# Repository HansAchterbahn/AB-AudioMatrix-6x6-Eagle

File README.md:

# AB AudioMatrix 6x6

Active audio matrix (6x6), which can map 6 input channels to 6 output channels. Connection via 3.5 jack cable. Compatible with line signals (aux, headphones, active speakers, ...).

*Fork me and have fun!*

## Pictures

## Schematic

## Board

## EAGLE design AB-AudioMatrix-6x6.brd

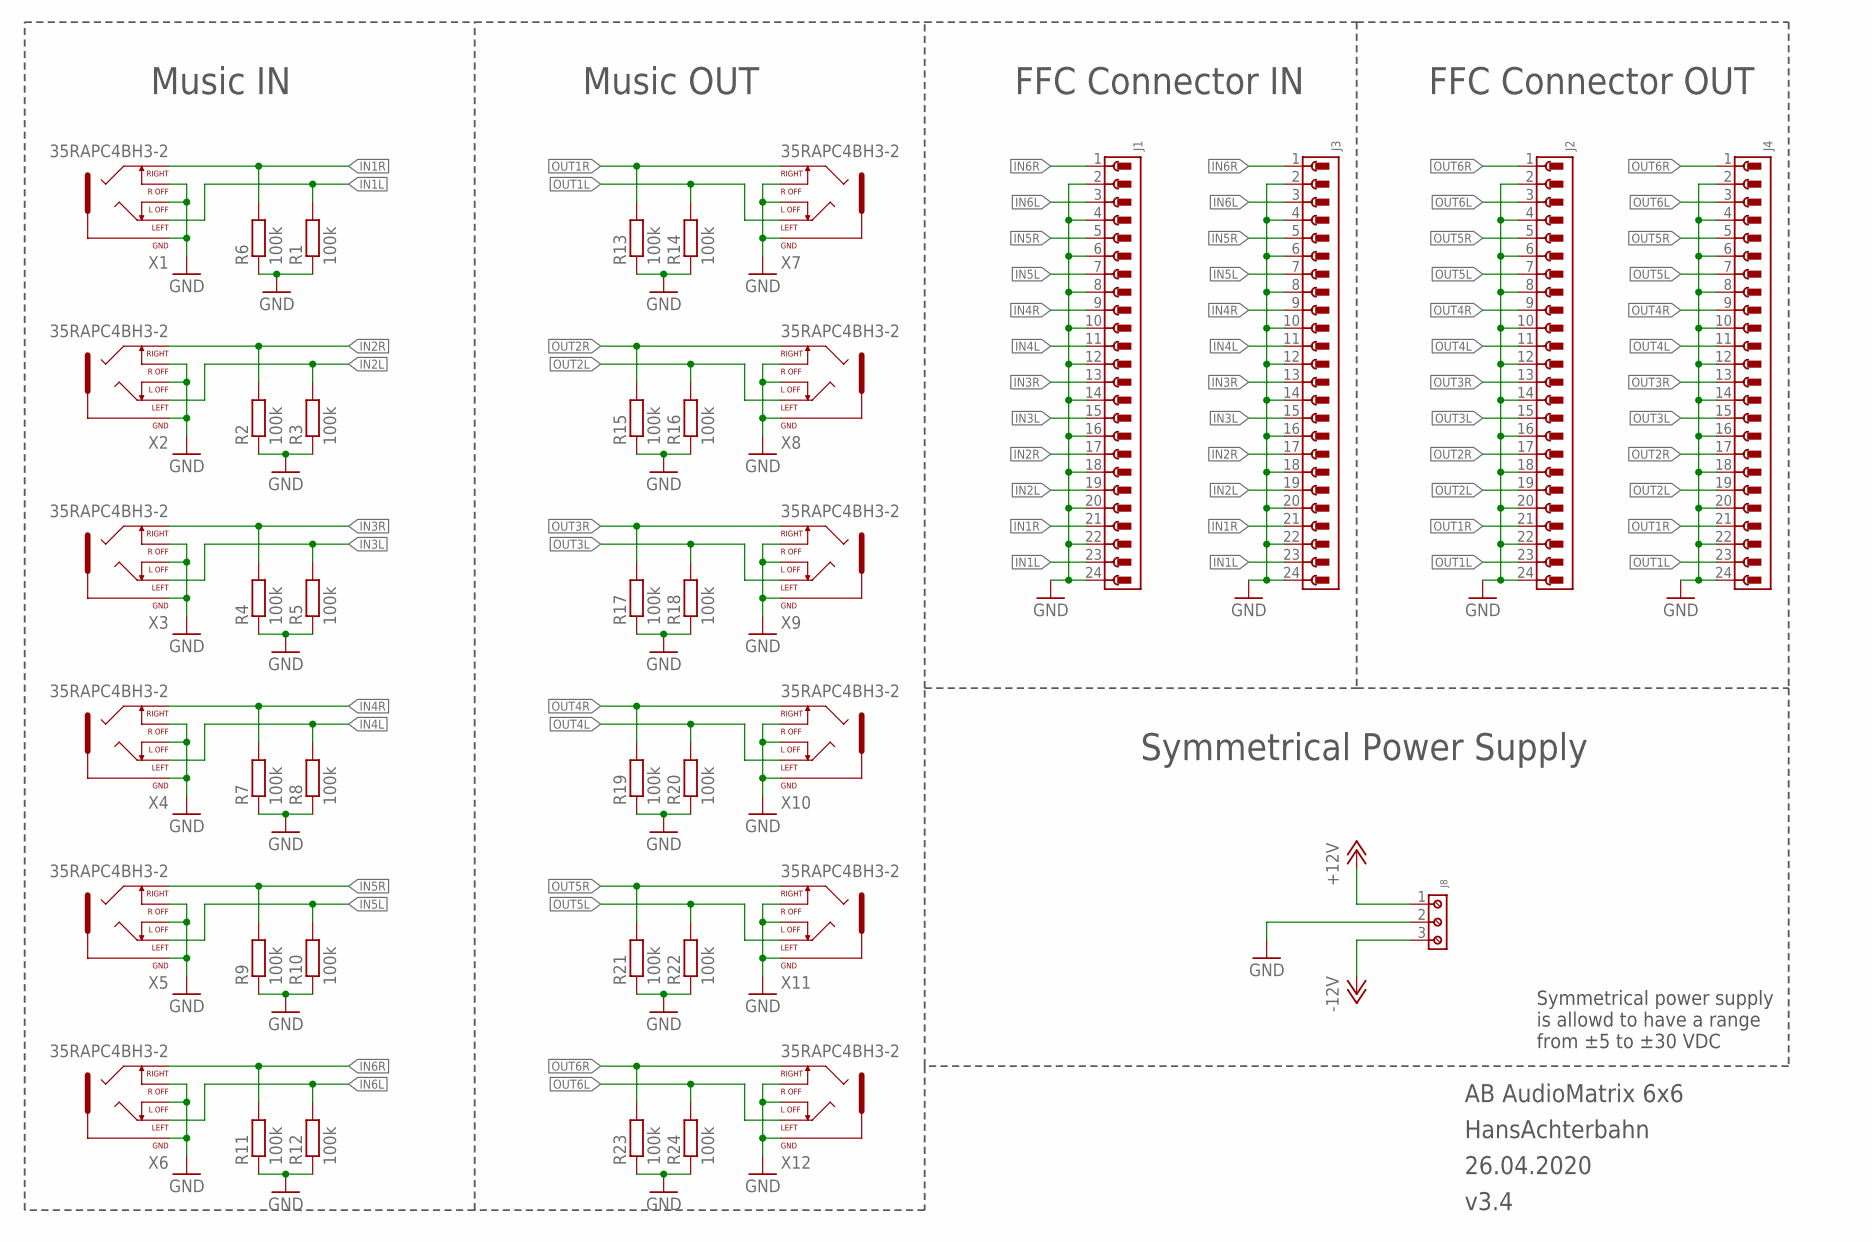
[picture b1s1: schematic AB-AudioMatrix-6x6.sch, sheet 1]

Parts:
J1, J2, J3, J4: 6861XX188622_686124188622; 686124188622
J8: 691102710003
R1, R2, R3, R4, R5, R6, R7, R8, R9, R10, R11, R12, R13, R14, R15, R16, R17, R18, R19, R20, R21, R22, R23, R24: 100k; R0603; MOUSER 71-CRCW0603-100K-E3
X1: 35RAPC4BH3-2; SWITCHCRAFT_35RAPC4BH3; MOUSER 502-35RAPC4BH3
X2, X3, X4, X5, X6, X7, X8, X9, X10, X11, X12: 35RAPC4BH3-2; SWITCHCRAFT_35RAPC4BH3

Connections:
+12V: J8.1; also elsewhere on the board
-12V: J8.3; also elsewhere on the board
GND: J1.2, J1.4, J1.6, J1.8, J1.10, J1.12, J1.14, J1.16, J1.18, J1.20, J1.22, J1.24, J2.2, J2.4, J2.6, J2.8, J2.10, J2.12, J2.14, J2.16, J2.18, J2.20, J2.22, J2.24, J3.2, J3.4, J3.6, J3.8, J3.10, J3.12, J3.14, J3.16, J3.18, J3.20, J3.22, J3.24, J4.2, J4.4, J4.6, J4.8, J4.10, J4.12, J4.14, J4.16, J4.18, J4.20, J4.22, J4.24, J8.2, R1.1, R2.1, R3.1, R4.1, R5.1, R6.1, R7.1, R8.1, R9.1, R10.1, R11.1, R12.1, R13.1, R14.1, R15.1, R16.1, R17.1, R18.1, R19.1, R20.1, R21.1, R22.1, R23.1, R24.1, X1.1 (GND), X1.3 (RIGHT_OFF), X1.4 (LEFT_OFF), X2.1 (GND), X2.3 (RIGHT_OFF), X2.4 (LEFT_OFF), X3.1 (GND), X3.3 (RIGHT_OFF), X3.4 (LEFT_OFF), X4.1 (GND), X4.3 (RIGHT_OFF), X4.4 (LEFT_OFF), X5.1 (GND), X5.3 (RIGHT_OFF), X5.4 (LEFT_OFF), X6.1 (GND), X6.3 (RIGHT_OFF), X6.4 (LEFT_OFF), X7.1 (GND), X7.3 (RIGHT_OFF), X7.4 (LEFT_OFF), X8.1 (GND), X8.3 (RIGHT_OFF), X8.4 (LEFT_OFF), X9.1 (GND), X9.3 (RIGHT_OFF), X9.4 (LEFT_OFF), X10.1 (GND), X10.3 (RIGHT_OFF), X10.4 (LEFT_OFF), X11.1 (GND), X11.3 (RIGHT_OFF), X11.4 (LEFT_OFF), X12.1 (GND), X12.3 (RIGHT_OFF), X12.4 (LEFT_OFF)
IN1L: J1.23, J3.23, R1.2, X1.5 (LEFT); also elsewhere on the board
IN1R: J1.21, J3.21, R6.2, X1.2 (RIGHT); also elsewhere on the board
IN2L: J1.19, J3.19, R3.2, X2.5 (LEFT); also elsewhere on the board
IN2R: J1.17, J3.17, R2.2, X2.2 (RIGHT); also elsewhere on the board
IN3L: J1.15, J3.15, R5.2, X3.5 (LEFT); also elsewhere on the board
IN3R: J1.13, J3.13, R4.2, X3.2 (RIGHT); also elsewhere on the board
IN4L: J1.11, J3.11, R8.2, X4.5 (LEFT); also elsewhere on the board
IN4R: J1.9, J3.9, R7.2, X4.2 (RIGHT); also elsewhere on the board
IN5L: J1.7, J3.7, R10.2, X5.5 (LEFT); also elsewhere on the board
IN5R: J1.5, J3.5, R9.2, X5.2 (RIGHT); also elsewhere on the board
IN6L: J1.3, J3.3, R12.2, X6.5 (LEFT); also elsewhere on the board
IN6R: J1.1, J3.1, R11.2, X6.2 (RIGHT); also elsewhere on the board
OUT1L: J2.23, J4.23, R14.2, X7.5 (LEFT); also elsewhere on the board
OUT1R: J2.21, J4.21, R13.2, X7.2 (RIGHT); also elsewhere on the board
OUT2L: J2.19, J4.19, R16.2, X8.5 (LEFT); also elsewhere on the board
OUT2R: J2.17, J4.17, R15.2, X8.2 (RIGHT); also elsewhere on the board
OUT3L: J2.15, J4.15, R18.2, X9.5 (LEFT); also elsewhere on the board
OUT3R: J2.13, J4.13, R17.2, X9.2 (RIGHT); also elsewhere on the board
OUT4L: J2.11, J4.11, R20.2, X10.5 (LEFT); also elsewhere on the board
OUT4R: J2.9, J4.9, R19.2, X10.2 (RIGHT); also elsewhere on the board
OUT5L: J2.7, J4.7, R22.2, X11.5 (LEFT); also elsewhere on the board
OUT5R: J2.5, J4.5, R21.2, X11.2 (RIGHT); also elsewhere on the board
OUT6L: J2.3, J4.3, R24.2, X12.5 (LEFT); also elsewhere on the board
OUT6R: J2.1, J4.1, R23.2, X12.2 (RIGHT); also elsewhere on the board

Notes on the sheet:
Music OUT
Music IN
FFC Connector IN
FFC Connector OUT
Symmetrical Power Supply
Symmetrical power supply is allowd to have a range from ±5 to ±30 VDC

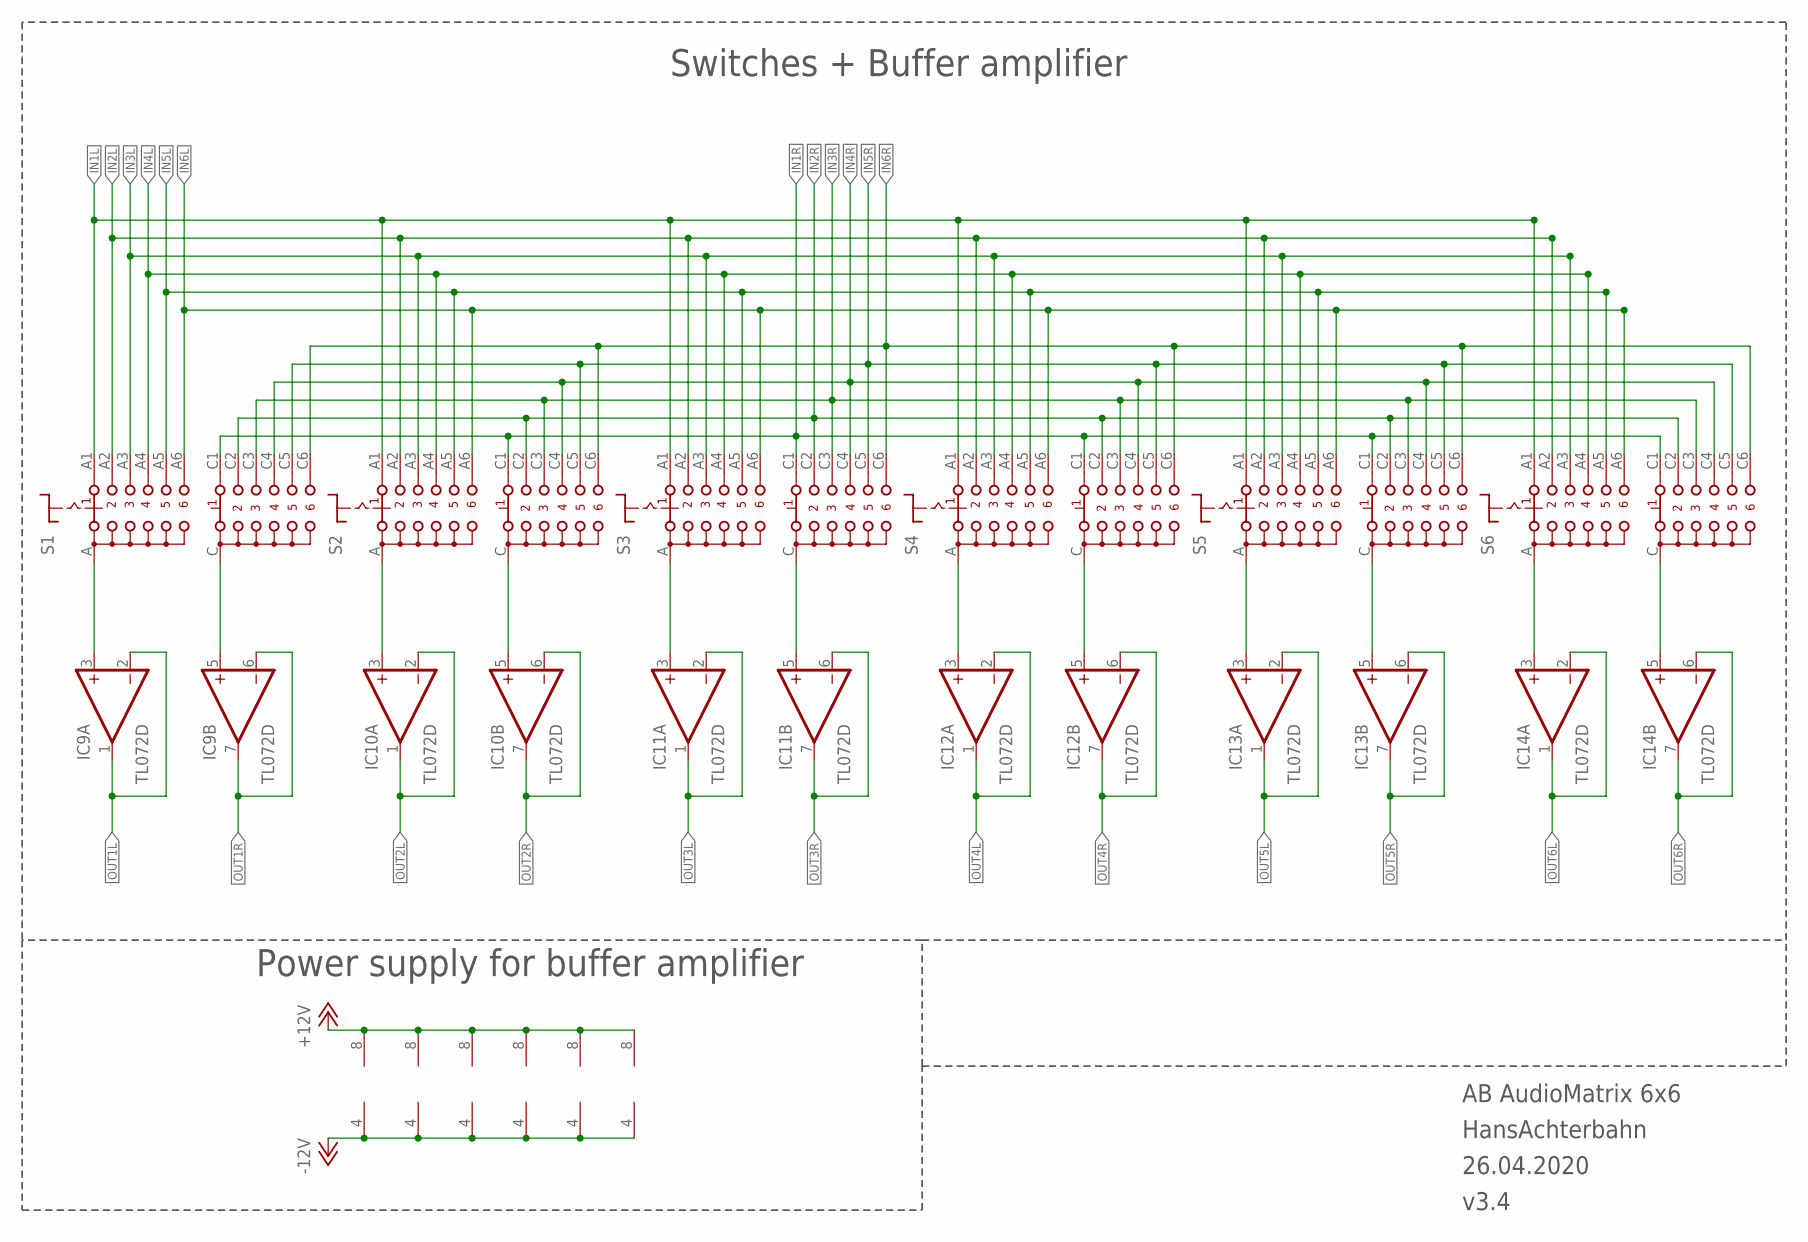
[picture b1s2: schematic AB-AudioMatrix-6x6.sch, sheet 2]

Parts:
IC9, IC10, IC11, IC12, IC13, IC14: TL072D; SO08
S1, S2, S3, S4, S5, S6: CK102X06

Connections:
+12V: IC9.8 (V+), IC10.8 (V+), IC11.8 (V+), IC12.8 (V+), IC13.8 (V+), IC14.8 (V+); also elsewhere on the board
-12V: IC9.4 (V-), IC10.4 (V-), IC11.4 (V-), IC12.4 (V-), IC13.4 (V-), IC14.4 (V-); also elsewhere on the board
IN1L: S1.A1, S2.A1, S3.A1, S4.A1, S5.A1, S6.A1; also elsewhere on the board
IN1R: S1.C1, S2.C1, S3.C1, S4.C1, S5.C1, S6.C1; also elsewhere on the board
IN2L: S1.A2, S2.A2, S3.A2, S4.A2, S5.A2, S6.A2; also elsewhere on the board
IN2R: S1.C2, S2.C2, S3.C2, S4.C2, S5.C2, S6.C2; also elsewhere on the board
IN3L: S1.A3, S2.A3, S3.A3, S4.A3, S5.A3, S6.A3; also elsewhere on the board
IN3R: S1.C3, S2.C3, S3.C3, S4.C3, S5.C3, S6.C3; also elsewhere on the board
IN4L: S1.A4, S2.A4, S3.A4, S4.A4, S5.A4, S6.A4; also elsewhere on the board
IN4R: S1.C4, S2.C4, S3.C4, S4.C4, S5.C4, S6.C4; also elsewhere on the board
IN5L: S1.A5, S2.A5, S3.A5, S4.A5, S5.A5, S6.A5; also elsewhere on the board
IN5R: S1.C5, S2.C5, S3.C5, S4.C5, S5.C5, S6.C5; also elsewhere on the board
IN6L: S1.A6, S2.A6, S3.A6, S4.A6, S5.A6, S6.A6; also elsewhere on the board
IN6R: S1.C6, S2.C6, S3.C6, S4.C6, S5.C6, S6.C6; also elsewhere on the board
unnamed: IC14.5 (+IN), S6.C
unnamed: IC14.3 (+IN), S6.A
unnamed: IC13.3 (+IN), S5.A
unnamed: IC12.3 (+IN), S4.A
unnamed: IC9.3 (+IN), S1.A
unnamed: IC12.5 (+IN), S4.C
unnamed: IC10.3 (+IN), S2.A
unnamed: IC13.5 (+IN), S5.C
unnamed: IC11.5 (+IN), S3.C
unnamed: IC11.3 (+IN), S3.A
unnamed: IC10.5 (+IN), S2.C
unnamed: IC9.5 (+IN), S1.C
OUT1L: IC9.1 (OUT), IC9.2 (-IN); also elsewhere on the board
OUT1R: IC9.6 (-IN), IC9.7 (OUT); also elsewhere on the board
OUT2L: IC10.1 (OUT), IC10.2 (-IN); also elsewhere on the board
OUT2R: IC10.6 (-IN), IC10.7 (OUT); also elsewhere on the board
OUT3L: IC11.1 (OUT), IC11.2 (-IN); also elsewhere on the board
OUT3R: IC11.6 (-IN), IC11.7 (OUT); also elsewhere on the board
OUT4L: IC12.1 (OUT), IC12.2 (-IN); also elsewhere on the board
OUT4R: IC12.6 (-IN), IC12.7 (OUT); also elsewhere on the board
OUT5L: IC13.1 (OUT), IC13.2 (-IN); also elsewhere on the board
OUT5R: IC13.6 (-IN), IC13.7 (OUT); also elsewhere on the board
OUT6L: IC14.1 (OUT), IC14.2 (-IN); also elsewhere on the board
OUT6R: IC14.6 (-IN), IC14.7 (OUT); also elsewhere on the board

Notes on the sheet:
Switches + Buffer amplifier
Power supply for buffer amplifier

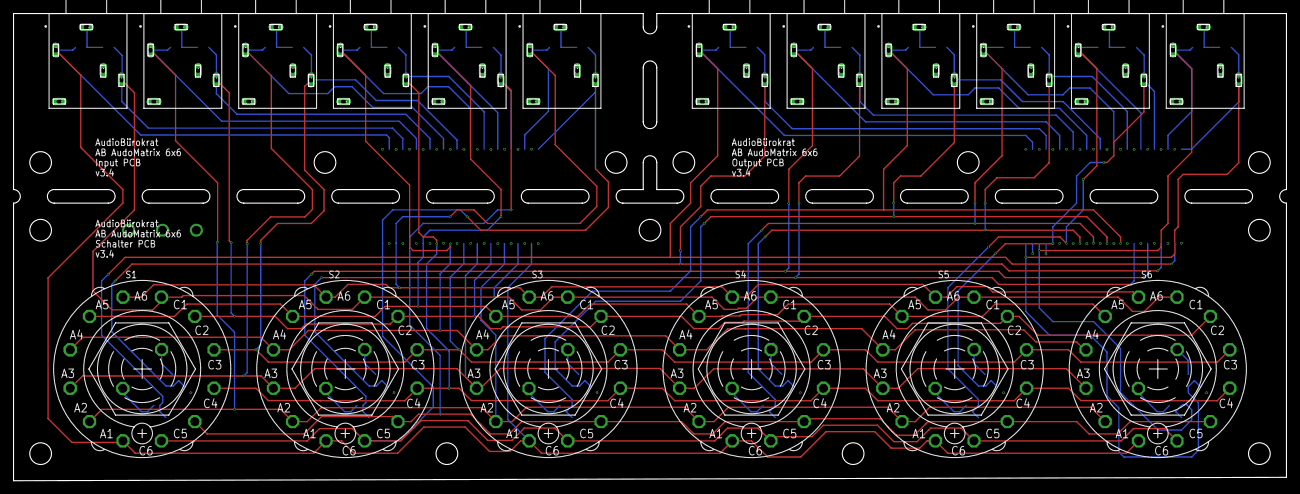
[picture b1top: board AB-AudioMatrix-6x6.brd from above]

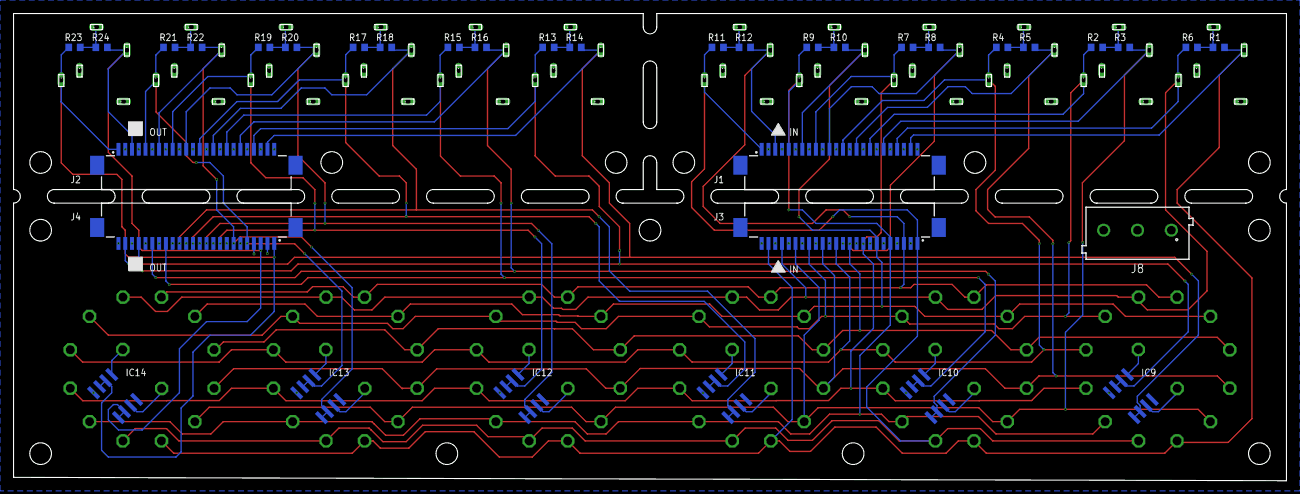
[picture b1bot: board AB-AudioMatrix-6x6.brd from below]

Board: 4 copper layers, 188.0 x 69.0 mm, 53 parts (35 on the bottom side), 39 nets.

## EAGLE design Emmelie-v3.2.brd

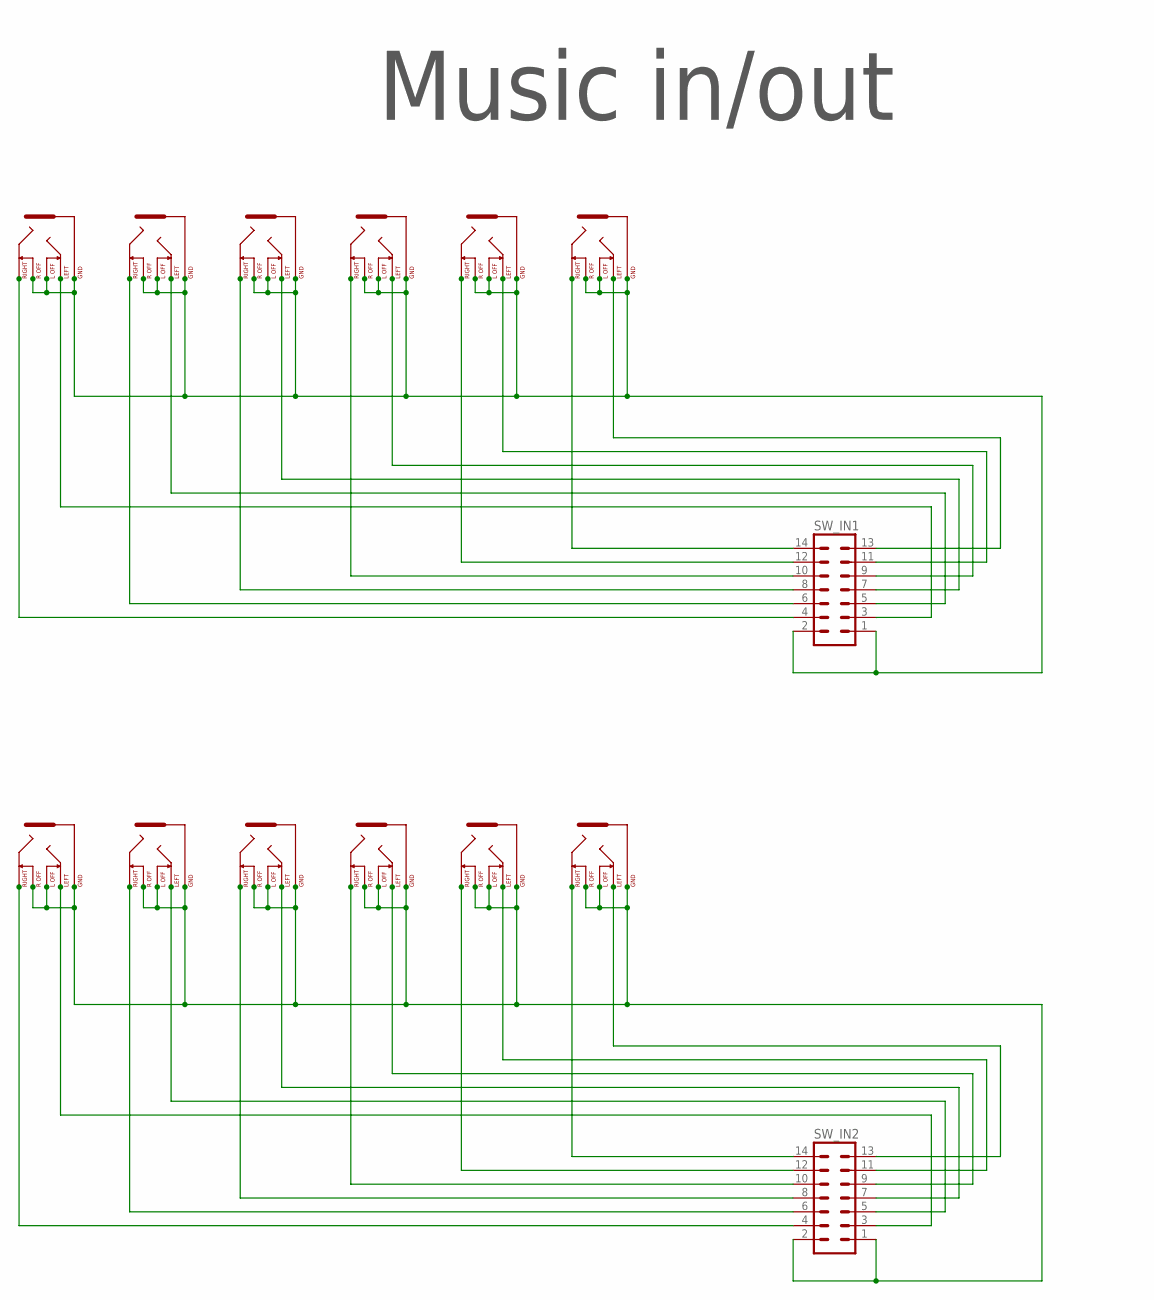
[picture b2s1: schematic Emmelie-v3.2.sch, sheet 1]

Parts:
SW_IN1, SW_IN2: ML14
U$1, U$2, U$3, U$4, U$5, U$6, U$7, U$8, U$9, U$10, U$11, U$12: KLINKE3,5

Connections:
KLINKE_IN_0V: SW_IN2.1, SW_IN2.2, U$7.GND, U$7.LEFT_OFF, U$7.RIGHT_OFF, U$8.GND, U$8.LEFT_OFF, U$8.RIGHT_OFF, U$9.GND, U$9.LEFT_OFF, U$9.RIGHT_OFF, U$10.GND, U$10.LEFT_OFF, U$10.RIGHT_OFF, U$11.GND, U$11.LEFT_OFF, U$11.RIGHT_OFF, U$12.GND, U$12.LEFT_OFF, U$12.RIGHT_OFF
KLINKE_OUT_0V: SW_IN1.1, SW_IN1.2, U$1.GND, U$1.LEFT_OFF, U$1.RIGHT_OFF, U$2.GND, U$2.LEFT_OFF, U$2.RIGHT_OFF, U$3.GND, U$3.LEFT_OFF, U$3.RIGHT_OFF, U$4.GND, U$4.LEFT_OFF, U$4.RIGHT_OFF, U$5.GND, U$5.LEFT_OFF, U$5.RIGHT_OFF, U$6.GND, U$6.LEFT_OFF, U$6.RIGHT_OFF
unnamed: SW_IN1.4, U$1.RIGHT
unnamed: SW_IN1.6, U$2.RIGHT
unnamed: SW_IN1.8, U$3.RIGHT
unnamed: SW_IN1.10, U$4.RIGHT
unnamed: SW_IN1.12, U$5.RIGHT
unnamed: SW_IN1.14, U$6.RIGHT
unnamed: SW_IN1.3, U$1.LEFT
unnamed: SW_IN1.5, U$2.LEFT
unnamed: SW_IN1.7, U$3.LEFT
unnamed: SW_IN1.9, U$4.LEFT
unnamed: SW_IN1.11, U$5.LEFT
unnamed: SW_IN1.13, U$6.LEFT
unnamed: SW_IN2.4, U$7.RIGHT
unnamed: SW_IN2.6, U$8.RIGHT
unnamed: SW_IN2.8, U$9.RIGHT
unnamed: SW_IN2.10, U$10.RIGHT
unnamed: SW_IN2.12, U$11.RIGHT
unnamed: SW_IN2.14, U$12.RIGHT
unnamed: SW_IN2.3, U$7.LEFT
unnamed: SW_IN2.5, U$8.LEFT
unnamed: SW_IN2.7, U$9.LEFT
unnamed: SW_IN2.9, U$10.LEFT
unnamed: SW_IN2.11, U$11.LEFT
unnamed: SW_IN2.13, U$12.LEFT

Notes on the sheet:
Music in/out

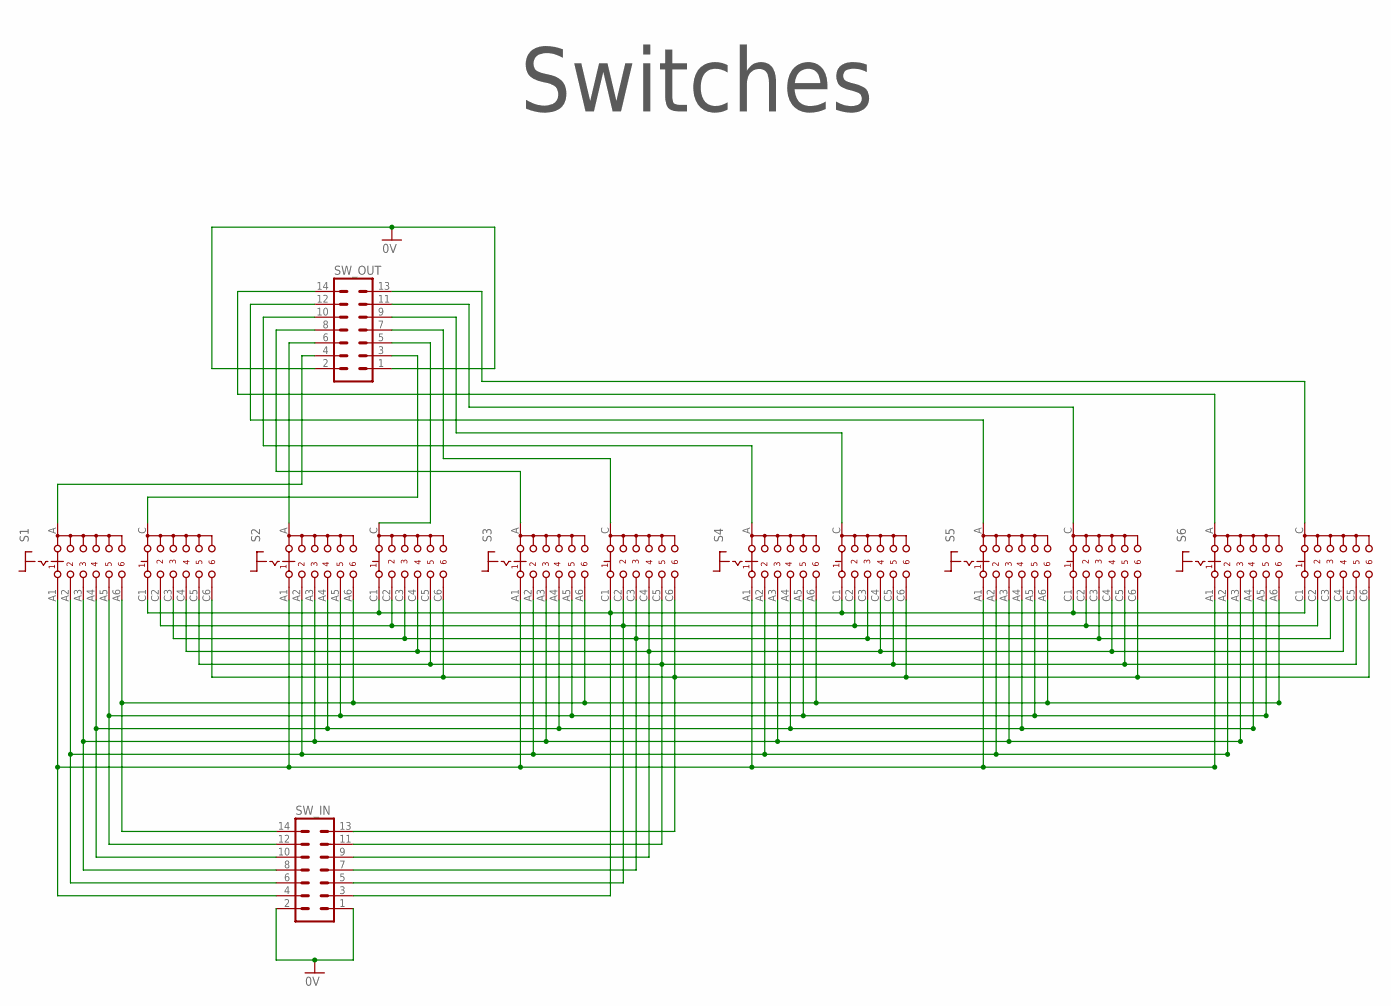
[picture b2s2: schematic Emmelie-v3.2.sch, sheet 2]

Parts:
S1, S2, S3, S4, S5, S6: CK102X06
SW_IN: ML14
SW_OUT: ML14

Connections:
unnamed: S1.A1, S2.A1, S3.A1, S4.A1, S5.A1, S6.A1, SW_IN.4
unnamed: S1.A2, S2.A2, S3.A2, S4.A2, S5.A2, S6.A2, SW_IN.6
unnamed: S1.A3, S2.A3, S3.A3, S4.A3, S5.A3, S6.A3, SW_IN.8
unnamed: S1.A4, S2.A4, S3.A4, S4.A4, S5.A4, S6.A4, SW_IN.10
unnamed: S1.A5, S2.A5, S3.A5, S4.A5, S5.A5, S6.A5, SW_IN.12
unnamed: S1.A6, S2.A6, S3.A6, S4.A6, S5.A6, S6.A6, SW_IN.14
unnamed: S1.C, SW_OUT.3
unnamed: S1.A, SW_OUT.4
unnamed: S2.A, SW_OUT.6
unnamed: S2.C, SW_OUT.5
unnamed: S3.A, SW_OUT.8
unnamed: S3.C, SW_OUT.7
unnamed: S4.A, SW_OUT.10
unnamed: S4.C, SW_OUT.9
unnamed: S5.A, SW_OUT.12
unnamed: S5.C, SW_OUT.11
unnamed: S6.A, SW_OUT.14
unnamed: S6.C, SW_OUT.13
unnamed: S1.C1, S2.C1, S3.C1, S4.C1, S5.C1, S6.C1, SW_IN.3
unnamed: S1.C2, S2.C2, S3.C2, S4.C2, S5.C2, S6.C2, SW_IN.5
unnamed: S1.C3, S2.C3, S3.C3, S4.C3, S5.C3, S6.C3, SW_IN.7
unnamed: S1.C4, S2.C4, S3.C4, S4.C4, S5.C4, S6.C4, SW_IN.9
unnamed: S1.C5, S2.C5, S3.C5, S4.C5, S5.C5, S6.C5, SW_IN.11
unnamed: S1.C6, S2.C6, S3.C6, S4.C6, S5.C6, S6.C6, SW_IN.13
SCHALTER_0V: SW_IN.1, SW_IN.2, SW_OUT.1, SW_OUT.2

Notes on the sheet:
Switches

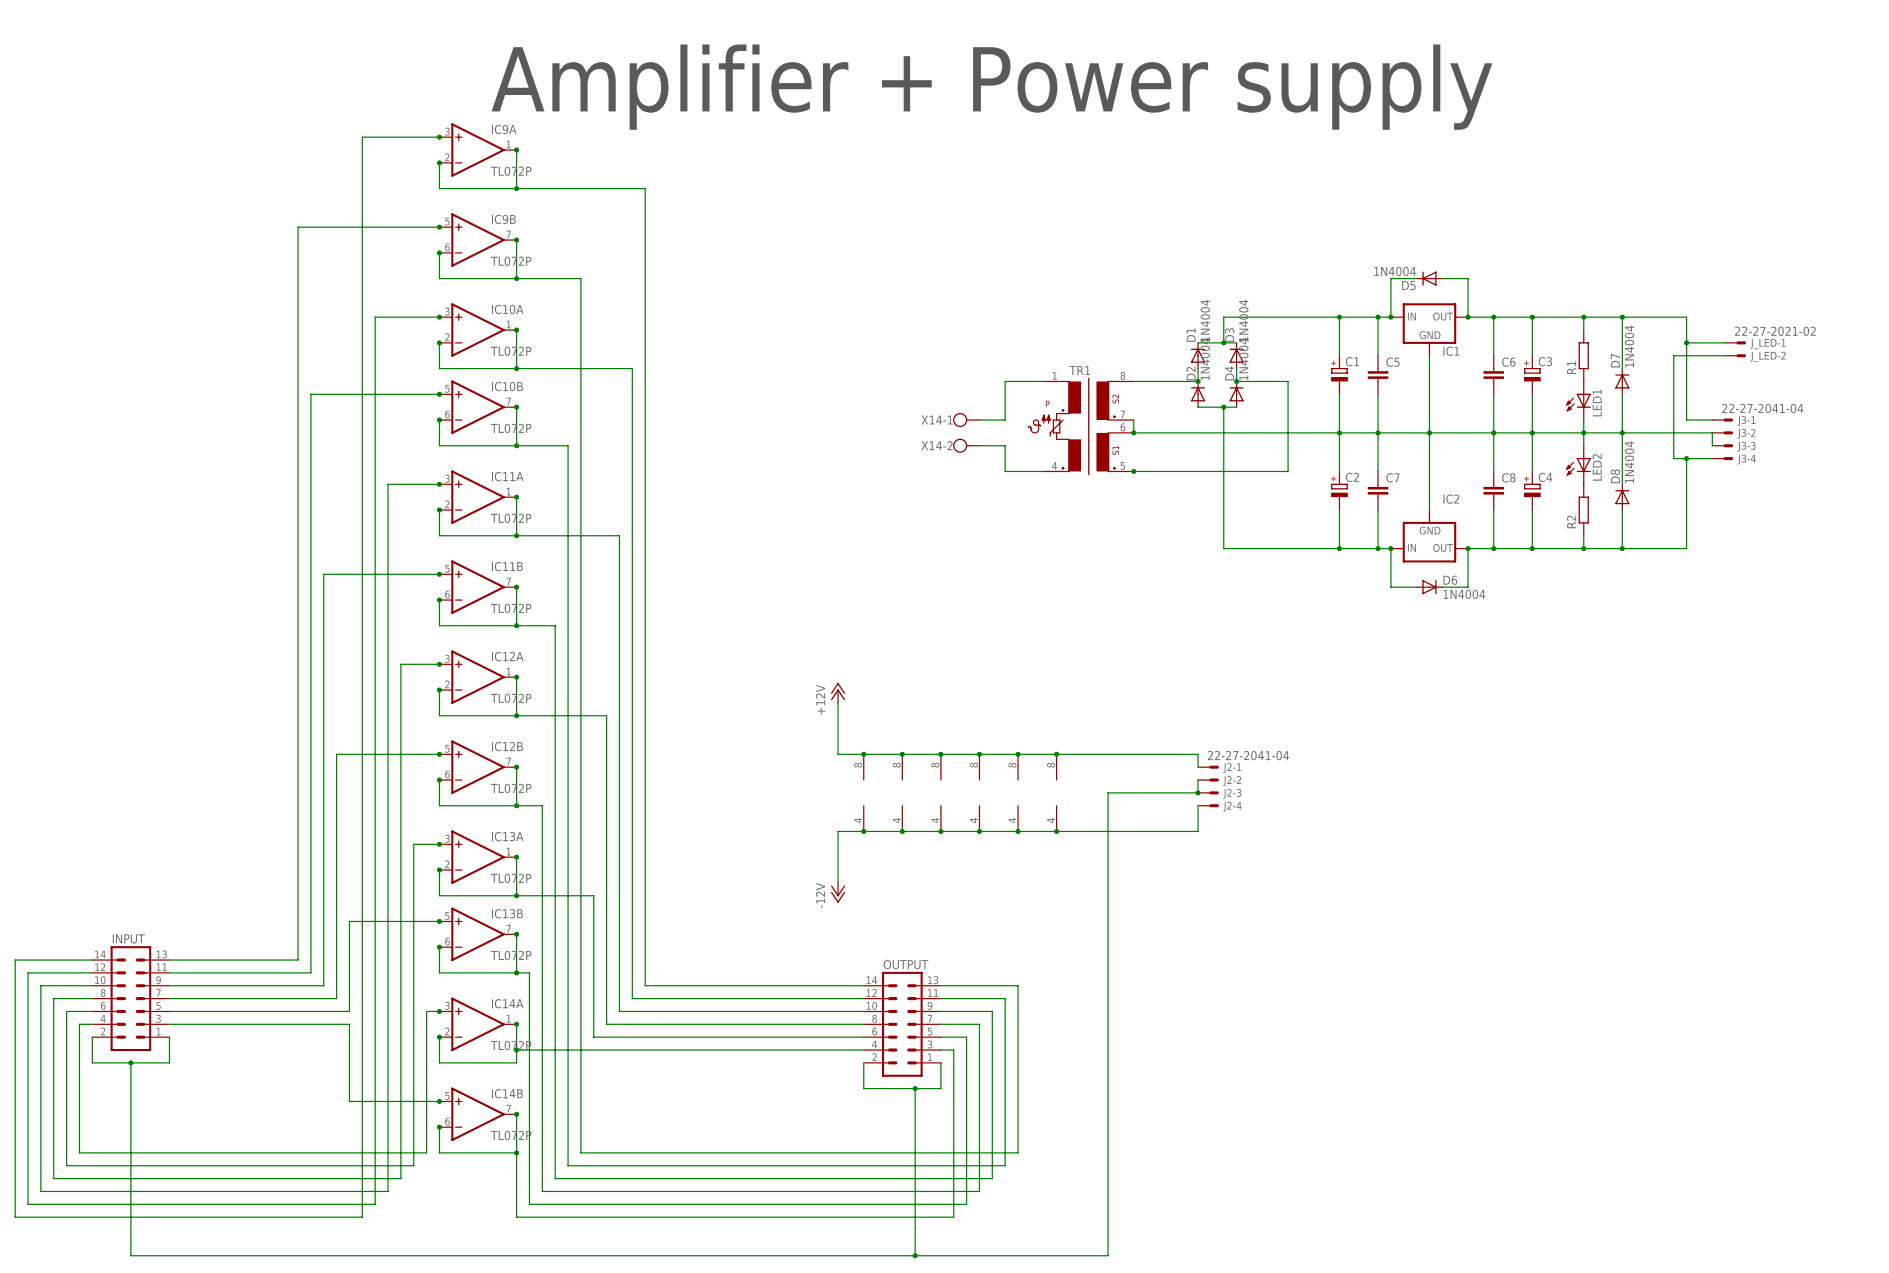
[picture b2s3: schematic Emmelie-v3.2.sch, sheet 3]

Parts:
C1, C2: CPOL-EUE5-13; E5-13
C3, C4: CPOL-EUE2.5-7; E2,5-7
C5, C6, C7, C8: C-EU050-075X075; C050-075X075
D1, D2, D3, D4, D5, D6, D7, D8: 1N4004; DO41-10
IC1: 78XXS
IC2: 79XXS
IC9, IC10, IC11, IC12, IC13, IC14: TL072P; DIL08
INPUT: ML14
J2, J3: 22-27-2041-04; 6410-04
J_LED: 22-27-2021-02; 6410-02
LED1, LED2: LED5MM
OUTPUT: ML14
R1, R2: R-EU_0207/15; 0207/15
TR1: FLE04-06
X14: W237-02P; W237-132

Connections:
+12V: IC9.8 (V+), IC10.8 (V+), IC11.8 (V+), IC12.8 (V+), IC13.8 (V+), IC14.8 (V+), J2.1
-12V: IC9.4 (V-), IC10.4 (V-), IC11.4 (V-), IC12.4 (V-), IC13.4 (V-), IC14.4 (V-), J2.4
unnamed: C2.-, C7.2, D2.A, D4.A, D6.A, IC2.IN
unnamed: D3.A, D4.C, TR1.5
unnamed: C1.+, C5.1, D1.C, D3.C, D5.C, IC1.IN
unnamed: LED1.A, R1.1
unnamed: LED2.K (C), R2.2
unnamed: TR1.1, X14.1
unnamed: D1.A, D2.C, TR1.8
unnamed: C3.+, C6.1, D5.A, D7.C, IC1.OUT, J3.1, J_LED.1, R1.2
unnamed: C4.-, C8.2, D6.C, D8.A, IC2.OUT, J3.4, J_LED.2, R2.1
unnamed: IC14.5 (+IN), INPUT.3
unnamed: IC14.3 (+IN), INPUT.4
unnamed: IC13.3 (+IN), INPUT.6
unnamed: IC12.3 (+IN), INPUT.8
unnamed: IC9.3 (+IN), INPUT.14
unnamed: IC12.5 (+IN), INPUT.7
unnamed: IC10.3 (+IN), INPUT.12
unnamed: IC13.5 (+IN), INPUT.5
unnamed: IC11.5 (+IN), INPUT.9
unnamed: IC11.3 (+IN), INPUT.10
unnamed: IC10.5 (+IN), INPUT.11
unnamed: IC9.5 (+IN), INPUT.13
unnamed: IC14.6 (-IN), IC14.7 (OUT), OUTPUT.3
unnamed: IC14.1 (OUT), IC14.2 (-IN), OUTPUT.4
unnamed: IC13.6 (-IN), IC13.7 (OUT), OUTPUT.5
unnamed: IC13.1 (OUT), IC13.2 (-IN), OUTPUT.6
unnamed: IC12.6 (-IN), IC12.7 (OUT), OUTPUT.7
unnamed: IC12.1 (OUT), IC12.2 (-IN), OUTPUT.8
unnamed: IC11.6 (-IN), IC11.7 (OUT), OUTPUT.9
unnamed: IC11.1 (OUT), IC11.2 (-IN), OUTPUT.10
unnamed: IC10.6 (-IN), IC10.7 (OUT), OUTPUT.11
unnamed: IC10.1 (OUT), IC10.2 (-IN), OUTPUT.12
unnamed: IC9.6 (-IN), IC9.7 (OUT), OUTPUT.13
unnamed: IC9.1 (OUT), IC9.2 (-IN), OUTPUT.14
unnamed: TR1.4, X14.2
NETZ_0V: C1.-, C2.+, C3.-, C4.+, C5.2, C6.2, C7.1, C8.1, D7.A, D8.C, IC1.GND, IC2.GND, J3.2, J3.3, LED1.K (C), LED2.A, TR1.6, TR1.7
OPV_0V: INPUT.1, INPUT.2, J2.2, J2.3, OUTPUT.1, OUTPUT.2

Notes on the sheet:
Amplifier + Power supply

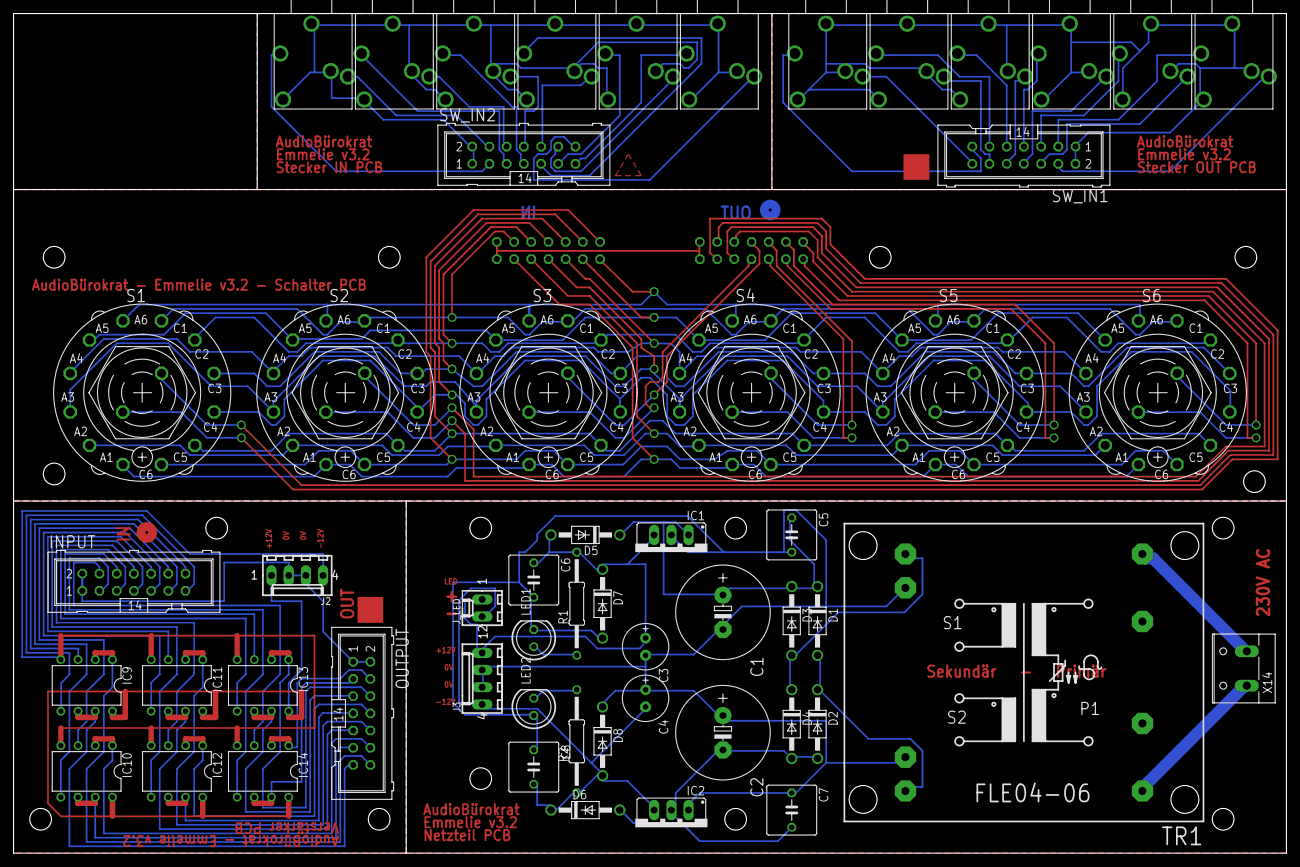
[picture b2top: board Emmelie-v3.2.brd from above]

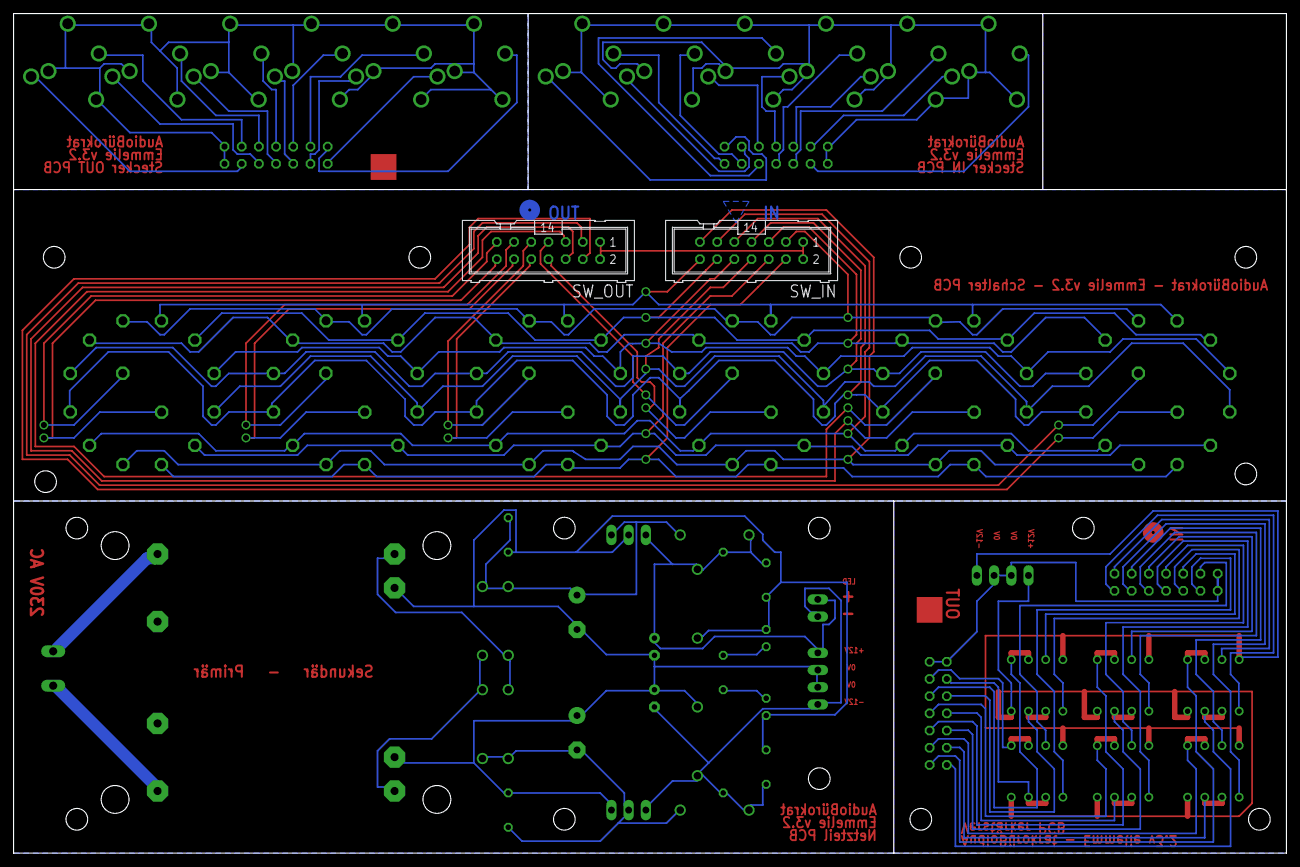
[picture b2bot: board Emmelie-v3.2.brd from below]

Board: 2 copper layers, 188.0 x 124.0 mm, 58 parts (2 on the bottom side), 89 nets.

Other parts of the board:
U$13: A4L-LOC

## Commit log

2019-03-22 Vorlage aus Emmelie-v3.1 von MH kopiert
2019-03-22 Optimierung für nicht durchkontaktierte Platinen
2019-03-22 Einbauplan
2019-03-22 Korrektur OPV PBC
2019-03-22 Korrektur OPV PBC 2
2019-03-22 Korrektur Folienkondensator Netzplatine
2019-03-22 Korrektur 12V + 230V Stecker
2019-03-22 Korrektur Stecker-Zuordnung
2019-03-22 Korrektur Klinken
2019-03-22 Korrektur Klinken 2
2019-03-22 Polygon
2019-03-22 Polygon 2
2019-03-22 Create LICENSE
2019-06-08 Changed README and added documentation folder "Doku" with pictures
2019-06-08 Old Eagle data converted to new Eagle XML data standard
2019-07-01 tidied up a little in schematic and board
2019-07-01 Update README | added images of schematic and board
2020-04-22 Neue Version v3.4 begonnen
2020-04-26 Platine grundlegend fertiggestellt
2020-04-30 3,5 mm Klinken Buchsen ausgetauscht | Spannungsversorgung hinzugefügt | Fusion 3D-Modell vollständig

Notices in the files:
parts and their libraries:
Wurth_Connectors_WR-FPC: Copyright: Würth Elektronik
